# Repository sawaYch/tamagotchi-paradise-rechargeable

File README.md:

# Tamagotchi Paradise — Rechargeable LiPo Mod

Replace the stock AAA cells with a USB-C rechargeable LiPo pack. This tutorial covers two circuit options: Simple Version / Use During Charge Version.

## Choosing a version

- Build **simple** if you mainly charge overnight with the unit off and want fewer solder joints.
- Build **use-during-charge** if you play while plugged in — the P-MOSFET path keeps charge current and load current separate so the cell is not needlessly cycled during USB sessions.

| Version               | Charge while playing?               | Extra parts                             | Best for                                                  |
| --------------------- | ----------------------------------- | --------------------------------------- | --------------------------------------------------------- |
| **Simple**            | Yes — but better to charge with the device **off**, otherwise the battery lifespan will decrease faster than expectation | Charger + battery + switch + buck-boost | First build, fewest parts                                 |
| **Use-during-charge** | Yes — dual power path               | Above + P-MOSFET + Schottky + pull-down | Everyday use without cycling the battery while plugged in |

---

## How it works

Stock Paradise runs from **2× AAA ≈ 3.0 V**. This mod:

1. Charges a **3.7 V LiPo** from USB-C via a **TP4057** module (charge + protection).
2. Regulates that rail to **3.0 V / 3.3 V** with a **TPS63802** buck-boost so the host sees a stable logic supply.
3. Uses a **side slide switch** as the main power cut (modified 2-pin use of the stock toggle footprint / a mini SPDT).

### Simple circuit

Power always comes from the charger’s protected **OUT** through the switch into the buck-boost. While USB is plugged in, the TP4057 both charges the pack **and** can supply the load from the same node — so **turn the Tamagotchi off while charging** for better battery life and cooler operation.

#### Simple wiring diagram

```mermaid
flowchart TB
  subgraph USB["USB Type-C female"]
    VBUS["VBUS (red)"]
    UGND["GND (black)"]
  end

  subgraph CHG["TP4057 charging module<br/>charge + battery protection"]
    INP["IN+"]
    INN["IN−"]
    BATP["BAT+"]
    BATN["BAT−"]
    OUTP["OUT+"]
    OUTN["OUT−"]
  end

  BAT["902030 LiPo<br/>500 mAh"]

  SW["Toggle / slide switch<br/>(modified 2-pin)<br/>middle ← OUT+ · right → VIN"]

  subgraph REG["TPS63802 Mini buck-boost<br/>regulates to 3.0 V / 3.3 V"]
    VIN["VIN"]
    RGND["GND"]
    VOUT["VOUT"]
    BGND["GND"]
  end

  TAMA["Tamagotchi Paradise<br/>host<br/>+ / −"]

  VBUS -->|red → IN+| INP
  UGND -->|black → IN−| INN
  BATP --> BAT
  BATN --> BAT
  OUTP -->|to middle pin| SW
  SW -->|right pin| VIN
  OUTN --> RGND
  VOUT --> TAMA
  BGND --> TAMA
```

#### Simple soldering map

Hold each module **silk / labels up**. Thick lines in the drawing are the hookup wires; dots are solder joints. There is **no** power-path PCB on this version.

Solder **1 → 3**, then **6 → 9**, then the LiPo (**4** and **5**) last.

1. Red: USB **VBUS** → TP4057 **IN+**
2. Black: USB **GND** → TP4057 **IN−**
3. Orange: TP4057 **OUT+** → switch **middle**
4. Red: LiPo **+** → TP4057 **BAT+**
5. Black: LiPo **−** → TP4057 **BAT−**
6. Orange: switch **right** → TPS63802 **VIN**
7. Red: TPS63802 **VOUT** → host **+**
8. Black: TP4057 **OUT−** → TPS63802 **GND**
9. Black: TPS63802 **GND** → host **−**

Ground is a chain (same net, three wires), not one shared rail. Host **+** / **−** are the leftover left-side springs (P6 / P7), screen facing you. Charge with the device **off**.

### Use-during-charge circuit

Two paths feed a shared **VSYS** node:

- **USB path:** `VBUS → SS14 Schottky → VSYS` — powers the device from USB while charging.
- **Battery path:** `TP4057 OUT+ → AO3401A (P-MOSFET) → VSYS` — powers the device from the LiPo when USB is unplugged.

When USB is present, **VBUS pulls the P-MOSFET gate high**, so the FET turns **off** and the LiPo is **not** loaded while it charges. When USB is removed, **R1 (100 kΩ)** pulls the gate to **GND**, the FET turns **on**, and the battery supplies VSYS.

#### Use-during-charge wiring diagram

```mermaid
flowchart TB
  subgraph charge["Charge"]
    direction LR
    USB["USB Type-C<br/>VBUS / GND"]
    CHG["TP4057<br/>IN / BAT / OUT"]
    CELL["902030 LiPo<br/>500 mAh"]
    USB -->|"VBUS to IN+<br/>GND to IN-"| CHG
    CHG <-->|"BAT+ / BAT-"| CELL
  end

  subgraph path["Power-path PCB  -  pads VBUS / BAT / VSYS / GND"]
    direction LR
    D1["D1 SS14<br/>USB: VBUS to VSYS"]
    Q1["Q1 AO3401A<br/>battery: OUT+ to VSYS<br/>gate from VBUS<br/>R1 100 k to GND"]
    VSYS(("VSYS"))
    D1 --> VSYS
    Q1 --> VSYS
  end

  subgraph out["Output"]
    direction LR
    SW["Slide switch<br/>middle / right"]
    REG["TPS63802<br/>VIN to VOUT<br/>3.0 V / 3.3 V"]
    HOST["Host + / -"]
    SW -->|right to VIN| REG
    REG -->|VOUT| HOST
    REG -->|GND| HOST
  end

  USB -->|VBUS| D1
  CHG -->|OUT+| Q1
  VSYS -->|middle| SW
  CHG -->|OUT- to PCB GND| path
  path -->|PCB GND to TPS GND| REG
```

#### Power-path truth table

| USB plugged in?             | Q1 (AO3401A[P-MOSFET]) | Device powered from | Battery                    |
| --------------------------- | ---------------------- | ------------------- | -------------------------- |
| Yes (VBUS high)             | **Off** (gate high)    | USB via **D1**      | Charging only (not loaded) |
| No (gate pulled down by R1) | **On**                 | LiPo via **Q1**     | Discharging into VSYS      |

Optional PCB for the power-path block only: see [`tama_power_path/`](tama_power_path/) (14×10 mm, pads `VBUS` / `BAT` / `VSYS` / `GND`).

#### Use-during-charge soldering map

Hold the assembled 14×10 mm board **silk up**. Thick lines in the drawing are the hookup wires; dots are solder joints. Match the pad names printed on your TP4057 / TPS63802 modules.

Solder **1 → 3**, then **6 → 11**, then the LiPo (**4** and **5**) last.

1. Red: USB **VBUS** = PCB **VBUS** = TP4057 **IN+**
2. Black: USB **GND** → TP4057 **IN−**
3. Blue: TP4057 **OUT+** → PCB **BAT**
4. Red: LiPo **+** → TP4057 **BAT+**
5. Black: LiPo **−** → TP4057 **BAT−**
6. Orange: PCB **VSYS** → switch **middle**
7. Orange: switch **right** → TPS63802 **VIN**
8. Red: TPS63802 **VOUT** → host **+**
9. Black: TP4057 **OUT−** → PCB **GND**
10. Black: PCB **GND** → TPS63802 **GND**
11. Black: TPS63802 **GND** → host **−**

Ground is a chain (same net, four wires), not one shared rail. PCB **GND** is required so **R1** can pull the FET gate down. Host **+** / **−** are the leftover left-side springs (P6 / P7), screen facing you.

---

## Parts list

### Common (both versions)

| Qty | Part                                                             | Notes                                                                                             |
| --- | ---------------------------------------------------------------- | ------------------------------------------------------------------------------------------------- |
| 1   | Tamagotchi Paradise                                              | Donor unit                                                                                        |
| 1   | USB Type-C female breakout / socket                              | Shell cutout on the side or bottom edge                                                           |
| 1   | TP4057 (or TP4056) LiPo charger + protection board               | Prefer modules with **IN / BAT / OUT** and DW01-style protection                                  |
| 1   | 902030 LiPo **3.7 V 500 mAh** (or similar that fits the AAA bay) | Use a **protected** pack or rely on the charger board’s protection                                |
| 1   | Mini slide switch (SPDT / SPST)                                  | Side cutout next to USB-C                                                                         |
| 1   | TPS63802 Mini buck-boost module                                  | Set / choose **3.0 V or 3.3 V** output                                                            |
| —   | Hookup wire (red / black), hot glue, Kapton tape                 | Strain relief + insulation                                                                        |
| —   | Tools                                                            | Screwdriver, soldering iron, flush cutters, needle files / Dremel, multimeter, ultra-sonic cutter |

### Extra for use-during-charge

| Qty | Part                    | Footprint / LCSC (KiCad BOM)                                       |
| --- | ----------------------- | ------------------------------------------------------------------ |
| 1   | **AO3401A** P-MOSFET    | SOT-23 · [C15127](https://www.lcsc.com/product-detail/C15127.html) |
| 1   | **SS14** Schottky diode | SMA · [C2480](https://www.lcsc.com/product-detail/C2480.html)      |
| 1   | **100 kΩ** resistor     | 0603 · [C25803](https://www.lcsc.com/product-detail/C25803.html)   |

Gerbers / CPL / BOM for the tiny power-path PCB: [`tama_power_path/fab/`](tama_power_path/fab/).

---

## Safety

- LiPo cells can ignite if shorted, crushed, or charged incorrectly. Work on a non-flammable surface; never leave a first charge unattended.
- Confirm **polarity** with a multimeter before closing the shell. Reversed battery wires will destroy the charger board and can damage the Paradise PCB.
- Do **not** hot-plug wires on a charged pack. Connect battery last; disconnect battery first when reworking.
- Keep metal tools and screws away from the exposed LiPo pouch and charger pads.
- If the pack swells, gets hot, or the charger LED behaves oddly, unplug USB and stop.

---

## Disassembly and Shell modification

1. Remove both AAA cells.
2. Remove the AAA battery case. Using ultra sonic cutter make you easier to remove the redundant shell plastic parts.
3. Remove the stock **+** and **−** spring contacts on the right hand side in terms of the screen facing to you side. The spring contacts is single piece of metal. Do not remove the one on left hand side, those are used for wiring the Power and GND.
4. Cut two adjacent rectangular openings on the side (or bottom edge) of the translucent shell
   - **USB-C** — sized to the female connector body so it sits flush / slightly recessed.
   - **Slide switch** — immediately above or beside the USB-C cutout.

---

## First power-on checklist

1. Switch **off**. No USB yet.
2. Measure LiPo voltage at **BAT+/BAT−** (typically ~3.7 V for a partial charge; do not connect a 0 V / damaged cell).
3. Plug in USB-C. Confirm the TP4057 charge LED (often red = charging, blue/green = done — check your module).
4. Measure **VSYS** (use-during-charge) or **OUT+** (simple): should rise with USB present.
5. Measure TPS63802 **VOUT** ≈ **3.0–3.3 V**.
6. Flip the slide switch **on**. Paradise should boot.
7. Unplug USB (use-during-charge): device should keep running from the LiPo without reboot if VSYS stayed up.
8. When the battery is charging, the red LED should light up. When the battery full of charge, a blue LED should light up.

<div style="display: flex; gap: 0px;">

</div>

---

## Repository layout

```
docs/                     Photos + soldering maps
  simple-solder.svg
  use-during-charge-solder.svg
tama_power_path/          KiCad project for the dual power-path PCB
  fab/                    Gerbers, BOM, CPL for ordering
```

---

## Disclaimer

This is an unofficial hardware modification. Opening the device voids warranties, risks permanent damage, and involves lithium batteries. Proceed only if you are comfortable with fine soldering and LiPo safety practices.

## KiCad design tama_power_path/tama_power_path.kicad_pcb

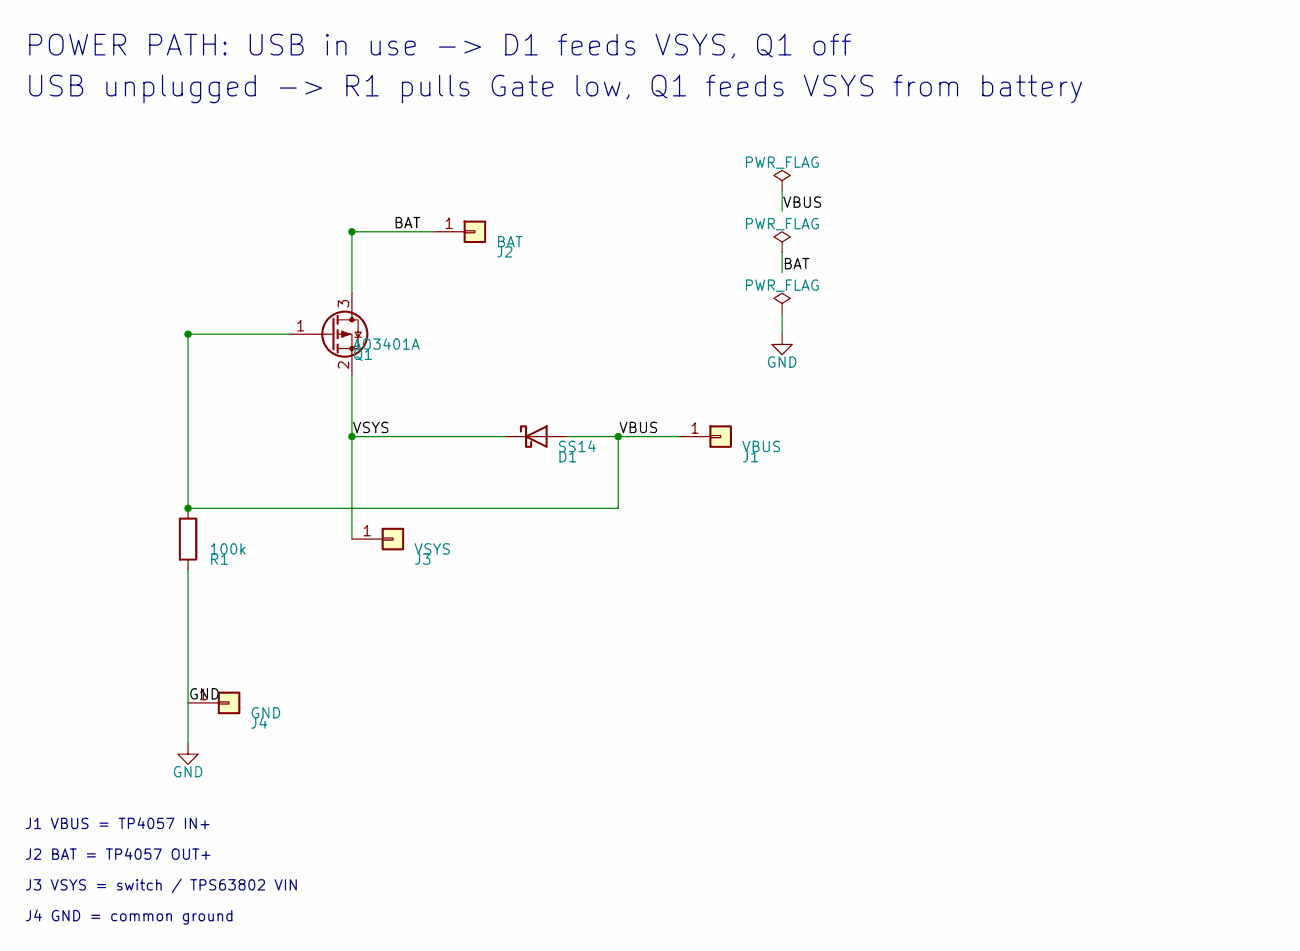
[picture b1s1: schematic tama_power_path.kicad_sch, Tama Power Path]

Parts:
D1: SS14; D_SMA; LCSC C2480
J1: VBUS; WirePads_1x01
J2: BAT; WirePads_1x01
J3: VSYS; WirePads_1x01
J4: GND; WirePads_1x01
Q1: AO3401A; SOT-23; LCSC C15127
R1: 100k; R_0603_1608Metric; LCSC C25803

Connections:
BAT: J2.1, Q1.3 (D)
GND: J4.1, R1.2
VBUS: D1.2 (A), J1.1, Q1.1 (G), R1.1
VSYS: D1.1 (K), J3.1, Q1.2 (S)

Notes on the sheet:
POWER PATH: USB in use -> D1 feeds VSYS, Q1 off
USB unplugged -> R1 pulls Gate low, Q1 feeds VSYS from battery
J1 VBUS = TP4057 IN+
J2 BAT = TP4057 OUT+
J3 VSYS = switch / TPS63802 VIN
J4 GND = common ground

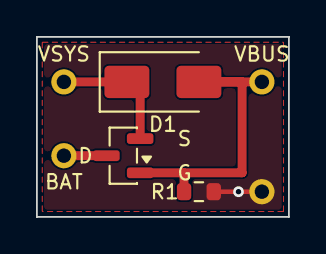
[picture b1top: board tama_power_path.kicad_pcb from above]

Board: 2 copper layers, 14.0 x 10.0 mm, 7 parts (0 on the bottom side), 4 nets.
